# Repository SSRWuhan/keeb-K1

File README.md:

# keeb-K1
This is my keyboard design for the KEEB program from Hack Club.

This is my very first keyboard! I have designed it so that you can have 6 configurable keys for macros or any other thing, along with joystick for scrolling or for using it as a mouse.

This was my first time making a PCB and writting firmware. Even though I already have experience with CAD, I did learn a few new things while making this.

NOTE: This project is still in active development as I still haven't made it in real life. Also, The firmware is complete, but support for vial is still in the works. Thus, `vial.json` won't work.

PCB:

Schematic:

Please check the attached BOM.csv file in the repo.

Additionally, the Onshape case files can be found here: [https://cad.onshape.com/documents/2183f5a9dc3f528ae43e5df6/w/0ccfa23a812405eb4031eeb2/e/91c99f1be3f6a34f9f2042e3](https://cad.onshape.com/documents/2183f5a9dc3f528ae43e5df6/w/0ccfa23a812405eb4031eeb2/e/91c99f1be3f6a34f9f2042e3)

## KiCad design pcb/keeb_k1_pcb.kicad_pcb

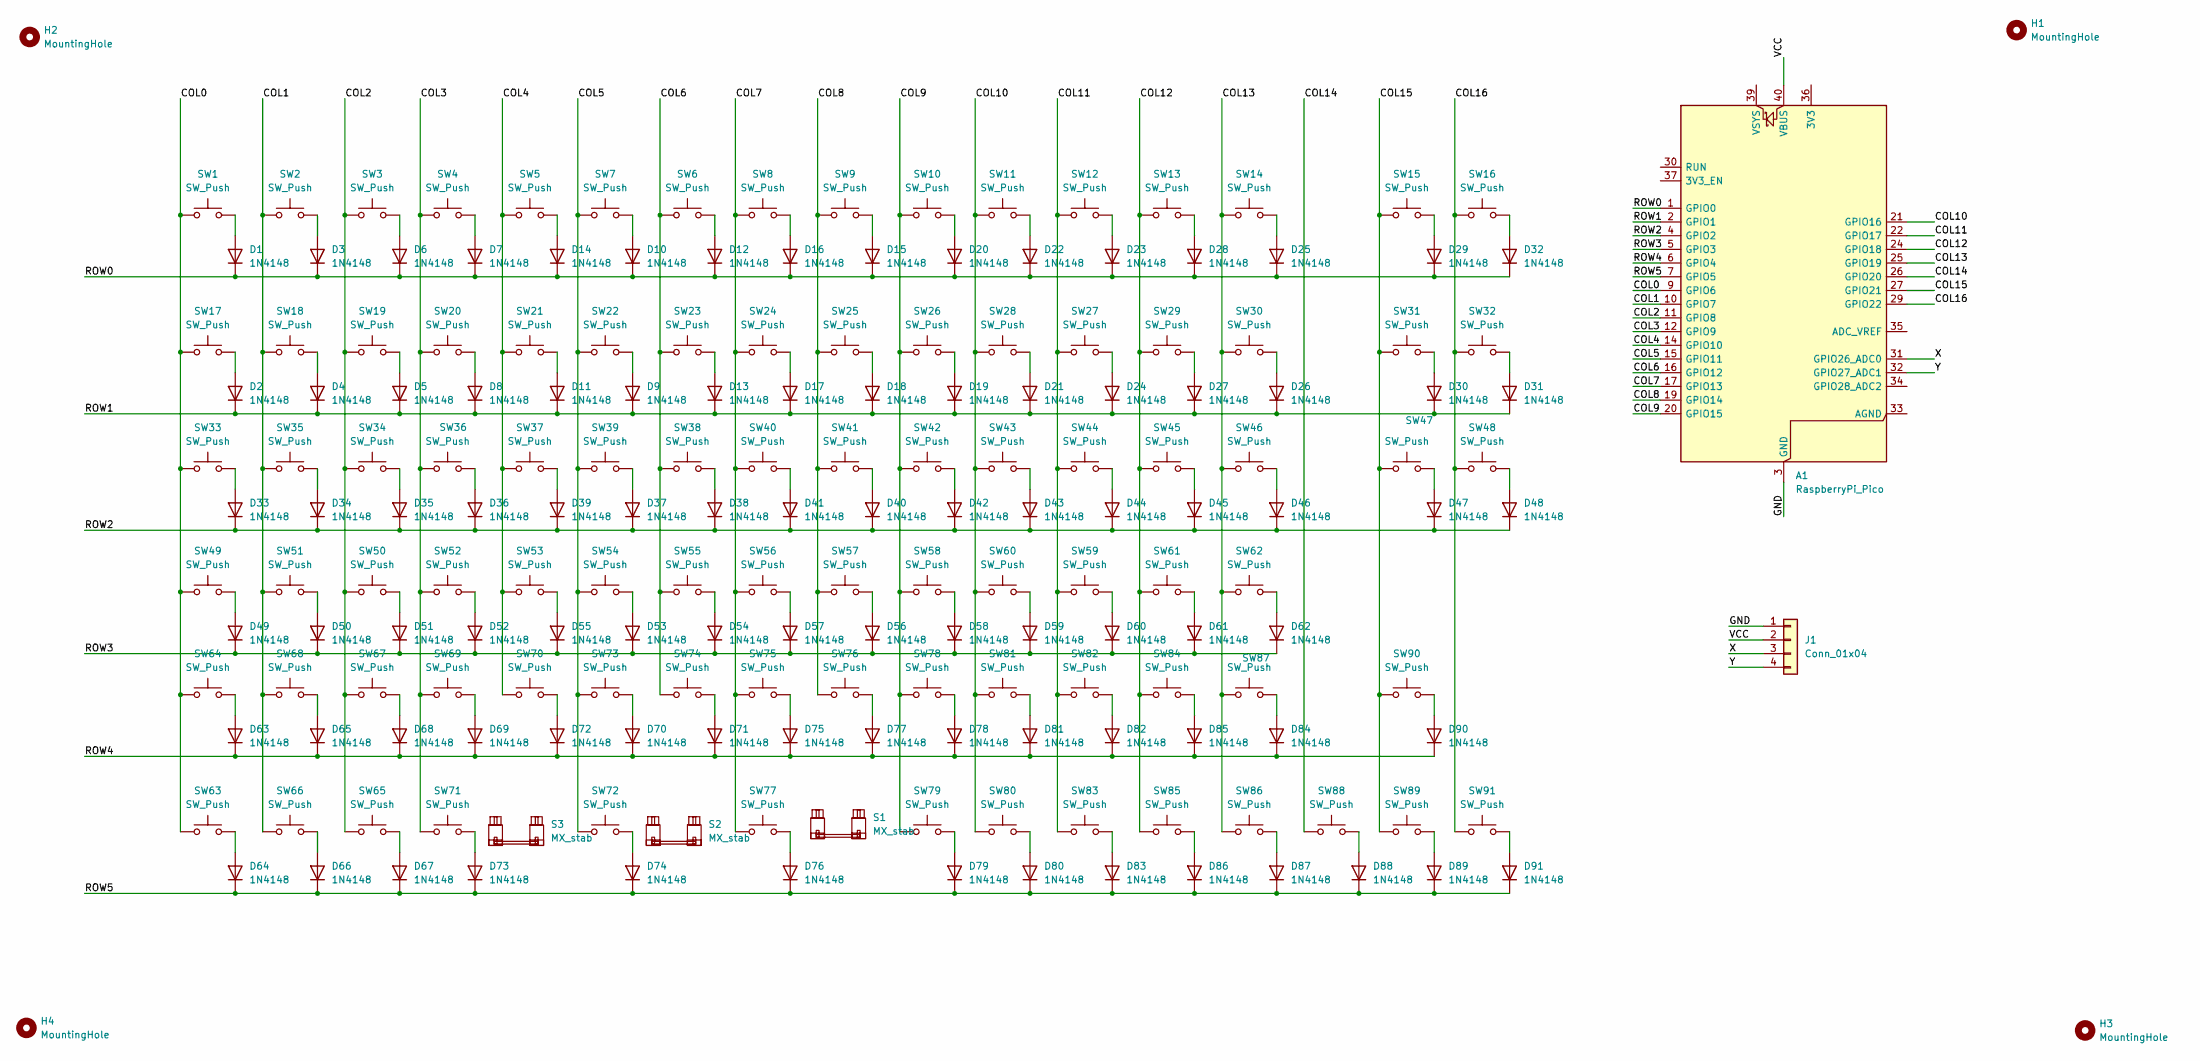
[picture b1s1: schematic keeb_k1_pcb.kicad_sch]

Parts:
A1: RaspberryPi_Pico; RaspberryPi_Pico_Common_THT
D1, D2, D3, D4, D5, D6, D7, D8, D9, D10, D11, D12, D13, D14, D15, D16, D17, D18, D19, D20, D21, D22, D23, D24, D25, D26, D27, D28, D29, D30, D31, D32, D33, D34, D35, D36, D37, D38, D39, D40, D41, D42, D43, D44, D45, D46, D47, D48, D49, D50, D51, D52, D53, D54, D55, D56, D57, D58, D59, D60, D61, D62, D63, D64, D65, D66, D67, D68, D69, D70, D71, D72, D73, D74, D75, D76, D77, D78, D79, D80, D81, D82, D83, D84, D85, D86, D87, D88, D89, D90, D91: 1N4148; D_DO-35_SOD27_P7.62mm_Horizontal
H1, H2, H3, H4: MountingHole; MountingHole_2.1mm
J1: Conn_01x04; PinHeader_1x04_P2.54mm_Vertical
S1, S2, S3: MX_stab; STAB_MX_P_2u
SW1, SW2, SW3, SW4, SW5, SW6, SW7, SW8, SW9, SW10, SW11, SW12, SW13, SW14, SW15, SW16, SW17, SW18, SW19, SW20, SW21, SW22, SW23, SW24, SW25, SW26, SW27, SW28, SW29, SW30, SW31, SW32, SW33, SW34, SW35, SW36, SW37, SW38, SW39, SW40, SW41, SW42, SW43, SW44, SW45, SW46, SW47, SW48, SW49, SW50, SW51, SW52, SW53, SW54, SW55, SW56, SW57, SW58, SW59, SW60, SW61, SW62, SW63, SW64, SW65, SW66, SW67, SW68, SW69, SW70, SW71, SW72, SW73, SW74, SW75, SW76, SW77, SW78, SW79, SW80, SW81, SW82, SW83, SW84, SW85, SW86, SW87, SW88, SW89, SW90, SW91: SW_Push; SW_MX_1u

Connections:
/COL0: A1.9 (GPIO6), SW1.1, SW17.1, SW33.1, SW49.1, SW63.1, SW64.1
/COL1: A1.10 (GPIO7), SW2.1, SW18.1, SW35.1, SW51.1, SW66.1, SW68.1
/COL2: A1.11 (GPIO8), SW3.1, SW19.1, SW34.1, SW50.1, SW65.1, SW67.1
/COL3: A1.12 (GPIO9), SW4.1, SW20.1, SW36.1, SW52.1, SW69.1, SW71.1
/COL4: A1.14 (GPIO10), SW5.1, SW21.1, SW37.1, SW53.1, SW70.1
/COL5: A1.15 (GPIO11), SW7.1, SW22.1, SW39.1, SW54.1, SW72.1, SW73.1
/COL6: A1.16 (GPIO12), SW6.1, SW23.1, SW38.1, SW55.1, SW74.1
/COL7: A1.17 (GPIO13), SW8.1, SW24.1, SW40.1, SW56.1, SW75.1, SW77.1
/COL8: A1.19 (GPIO14), SW9.1, SW25.1, SW41.1, SW57.1, SW76.1
/COL9: A1.20 (GPIO15), SW10.1, SW26.1, SW42.1, SW58.1, SW78.1, SW79.1
/COL10: A1.21 (GPIO16), SW11.1, SW28.1, SW43.1, SW60.1, SW80.1, SW81.1
/COL11: A1.22 (GPIO17), SW12.1, SW27.1, SW44.1, SW59.1, SW82.1, SW83.1
/COL12: A1.24 (GPIO18), SW13.1, SW29.1, SW45.1, SW61.1, SW84.1, SW85.1
/COL13: A1.25 (GPIO19), SW14.1, SW30.1, SW46.1, SW62.1, SW86.1, SW87.1
/COL14: A1.26 (GPIO20), SW88.1
/COL15: A1.27 (GPIO21), SW15.1, SW31.1, SW47.1, SW89.1, SW90.1
/COL16: A1.29 (GPIO22), SW16.1, SW32.1, SW48.1, SW91.1
/GND: A1.3 (GND), A1.8 (GND), A1.13 (GND), A1.18 (GND), A1.23 (GND), A1.28 (GND), A1.38 (GND), J1.1
/ROW0: A1.1 (GPIO0), D1.1 (K), D3.1 (K), D6.1 (K), D7.1 (K), D10.1 (K), D12.1 (K), D14.1 (K), D15.1 (K), D16.1 (K), D20.1 (K), D22.1 (K), D23.1 (K), D25.1 (K), D28.1 (K), D29.1 (K), D32.1 (K)
/ROW1: A1.2 (GPIO1), D2.1 (K), D4.1 (K), D5.1 (K), D8.1 (K), D9.1 (K), D11.1 (K), D13.1 (K), D17.1 (K), D18.1 (K), D19.1 (K), D21.1 (K), D24.1 (K), D26.1 (K), D27.1 (K), D30.1 (K), D31.1 (K)
/ROW2: A1.4 (GPIO2), D33.1 (K), D34.1 (K), D35.1 (K), D36.1 (K), D37.1 (K), D38.1 (K), D39.1 (K), D40.1 (K), D41.1 (K), D42.1 (K), D43.1 (K), D44.1 (K), D45.1 (K), D46.1 (K), D47.1 (K), D48.1 (K)
/ROW3: A1.5 (GPIO3), D49.1 (K), D50.1 (K), D51.1 (K), D52.1 (K), D53.1 (K), D54.1 (K), D55.1 (K), D56.1 (K), D57.1 (K), D58.1 (K), D59.1 (K), D60.1 (K), D61.1 (K), D62.1 (K)
/ROW4: A1.6 (GPIO4), D63.1 (K), D65.1 (K), D68.1 (K), D69.1 (K), D70.1 (K), D71.1 (K), D72.1 (K), D75.1 (K), D77.1 (K), D78.1 (K), D81.1 (K), D82.1 (K), D84.1 (K), D85.1 (K), D90.1 (K)
/ROW5: A1.7 (GPIO5), D64.1 (K), D66.1 (K), D67.1 (K), D73.1 (K), D74.1 (K), D76.1 (K), D79.1 (K), D80.1 (K), D83.1 (K), D86.1 (K), D87.1 (K), D88.1 (K), D89.1 (K), D91.1 (K)
/VCC: A1.40 (VBUS), J1.2
/X: A1.31 (GPIO26_ADC0), J1.3
/Y: A1.32 (GPIO27_ADC1), J1.4
unnamed: D1.2 (A), SW1.2
unnamed: D2.2 (A), SW17.2
unnamed: D3.2 (A), SW2.2
unnamed: D4.2 (A), SW18.2
unnamed: D5.2 (A), SW19.2
unnamed: D6.2 (A), SW3.2
unnamed: D7.2 (A), SW4.2
unnamed: D8.2 (A), SW20.2
unnamed: D9.2 (A), SW22.2
unnamed: D10.2 (A), SW7.2
unnamed: D11.2 (A), SW21.2
unnamed: D12.2 (A), SW6.2
unnamed: D13.2 (A), SW23.2
unnamed: D14.2 (A), SW5.2
unnamed: D15.2 (A), SW9.2
unnamed: D16.2 (A), SW8.2
unnamed: D17.2 (A), SW24.2
unnamed: D18.2 (A), SW25.2
unnamed: D19.2 (A), SW26.2
unnamed: D20.2 (A), SW10.2
unnamed: D21.2 (A), SW28.2
unnamed: D22.2 (A), SW11.2
unnamed: D23.2 (A), SW12.2
unnamed: D24.2 (A), SW27.2
unnamed: D25.2 (A), SW14.2
unnamed: D26.2 (A), SW30.2
unnamed: D27.2 (A), SW29.2
unnamed: D28.2 (A), SW13.2
unnamed: D29.2 (A), SW15.2
unnamed: D30.2 (A), SW31.2
unnamed: D31.2 (A), SW32.2
unnamed: D32.2 (A), SW16.2
unnamed: D33.2 (A), SW33.2
unnamed: D34.2 (A), SW35.2
unnamed: D35.2 (A), SW34.2
unnamed: D36.2 (A), SW36.2
unnamed: D37.2 (A), SW39.2
unnamed: D38.2 (A), SW38.2
unnamed: D39.2 (A), SW37.2
unnamed: D40.2 (A), SW41.2
unnamed: D41.2 (A), SW40.2
unnamed: D42.2 (A), SW42.2
unnamed: D43.2 (A), SW43.2
unnamed: D44.2 (A), SW44.2
unnamed: D45.2 (A), SW45.2
unnamed: D46.2 (A), SW46.2
unnamed: D47.2 (A), SW47.2
unnamed: D48.2 (A), SW48.2
unnamed: D49.2 (A), SW49.2
unnamed: D50.2 (A), SW51.2
unnamed: D51.2 (A), SW50.2
unnamed: D52.2 (A), SW52.2
unnamed: D53.2 (A), SW54.2
unnamed: D54.2 (A), SW55.2
unnamed: D55.2 (A), SW53.2
unnamed: D56.2 (A), SW57.2
unnamed: D57.2 (A), SW56.2
unnamed: D58.2 (A), SW58.2
unnamed: D59.2 (A), SW60.2
unnamed: D60.2 (A), SW59.2
unnamed: D61.2 (A), SW61.2
unnamed: D62.2 (A), SW62.2
unnamed: D63.2 (A), SW64.2
unnamed: D64.2 (A), SW63.2
unnamed: D65.2 (A), SW68.2
unnamed: D66.2 (A), SW66.2
unnamed: D67.2 (A), SW65.2
unnamed: D68.2 (A), SW67.2
unnamed: D69.2 (A), SW69.2
unnamed: D70.2 (A), SW73.2
unnamed: D71.2 (A), SW74.2
unnamed: D72.2 (A), SW70.2
unnamed: D73.2 (A), SW71.2
unnamed: D74.2 (A), SW72.2
unnamed: D75.2 (A), SW75.2
unnamed: D76.2 (A), SW77.2
unnamed: D77.2 (A), SW76.2
unnamed: D78.2 (A), SW78.2
unnamed: D79.2 (A), SW79.2
unnamed: D80.2 (A), SW80.2
unnamed: D81.2 (A), SW81.2
unnamed: D82.2 (A), SW82.2
unnamed: D83.2 (A), SW83.2
unnamed: D84.2 (A), SW87.2
unnamed: D85.2 (A), SW84.2
unnamed: D86.2 (A), SW85.2
unnamed: D87.2 (A), SW86.2
unnamed: D88.2 (A), SW88.2
unnamed: D89.2 (A), SW89.2
unnamed: D90.2 (A), SW90.2
unnamed: D91.2 (A), SW91.2

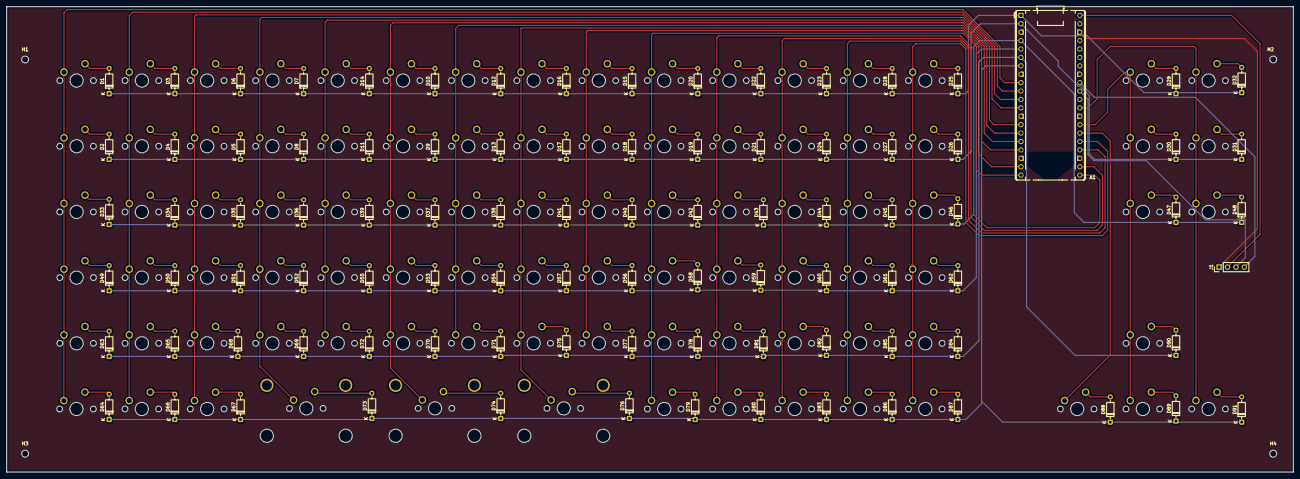
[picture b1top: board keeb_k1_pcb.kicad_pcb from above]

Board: 2 copper layers, 388.6 x 140.6 mm, 191 parts (0 on the bottom side), 118 nets.
